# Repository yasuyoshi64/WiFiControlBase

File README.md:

# sdkconfig
Serial flasher config

	Flash size				4MB

Partition Table

	Patition Table			Single factory app (large), no OTA

WiFiControlBase

	LED GPIO number			5

SD card PIN configuration

	MOSI GPIO number		17
	MOSO GPIO number		19
	CLK GPIO number			18
	CS GPIO number			16
	SD card sw GPIO number	4

OLED(SSD1306) PIN configuration

	I2C SDA GPIO number		21
	I2C SCL GPIO number		22

HTTP Server

	WebSocket server support	TRUE

FAT Filesystem support

	Long filename support	Long filename buffer in heap
	OEM Code Page			Japanese (DBCS) (CP932)

Color settings

	Color depth.			1: 1 byte per pixel

Font usage

Enable built-in fonts

	Enable UNSCII 8 (Perfect monospace font)	TRUE

3rd Party Libraries

	QR code library			TRUE

# 機能

## SDカードの内容

### ./config

```
ssid=[Wi-Fi SSID]
pass=[Wi-Fi Password]
```

### ./document

ここにはWeb用のファイルを格納します。

## 使い方

* 「No file」と表示されている場合はSDカードを挿入します。
* 「Wi-Fi Connecting」はWi-Fi接続中です。
* Wi-Fi接続完了後はQRコードが表示されます。QRコードを読み込むとWebのURLが読み込まれ、documentのWebが表示されます。
* QRコードは30秒で消灯します。GPIO0のボタンを押下すると再度30秒表示されます。
* SDカードは電源ON中でも抜き差し可能です。

## 回路図

## Web画面

ロード時にIPアドレスやチップ情報などを読み込み。
メモを入力してSaveボタンをクリックするとSDカードのsaveファイルに格納されます。
メモは再ロード時に読み込まれます。

# _Sample project_

(See the README.md file in the upper level 'examples' directory for more information about examples.)

This is the simplest buildable example. The example is used by command `idf.py create-project`
that copies the project to user specified path and set it's name. For more information follow the [docs page](https://docs.espressif.com/projects/esp-idf/en/latest/api-guides/build-system.html#start-a-new-project)

## How to use example
We encourage the users to use the example as a template for the new projects.
A recommended way is to follow the instructions on a [docs page](https://docs.espressif.com/projects/esp-idf/en/latest/api-guides/build-system.html#start-a-new-project).

## Example folder contents

The project **sample_project** contains one source file in C language [main.c](main/main.c). The file is located in folder [main](main).

ESP-IDF projects are built using CMake. The project build configuration is contained in `CMakeLists.txt`
files that provide set of directives and instructions describing the project's source files and targets
(executable, library, or both). 

Below is short explanation of remaining files in the project folder.

```
├── CMakeLists.txt
├── main
│   ├── CMakeLists.txt
│   └── main.c
└── README.md                  This is the file you are currently reading
```
Additionally, the sample project contains Makefile and component.mk files, used for the legacy Make based build system. 
They are not used or needed when building with CMake and idf.py.

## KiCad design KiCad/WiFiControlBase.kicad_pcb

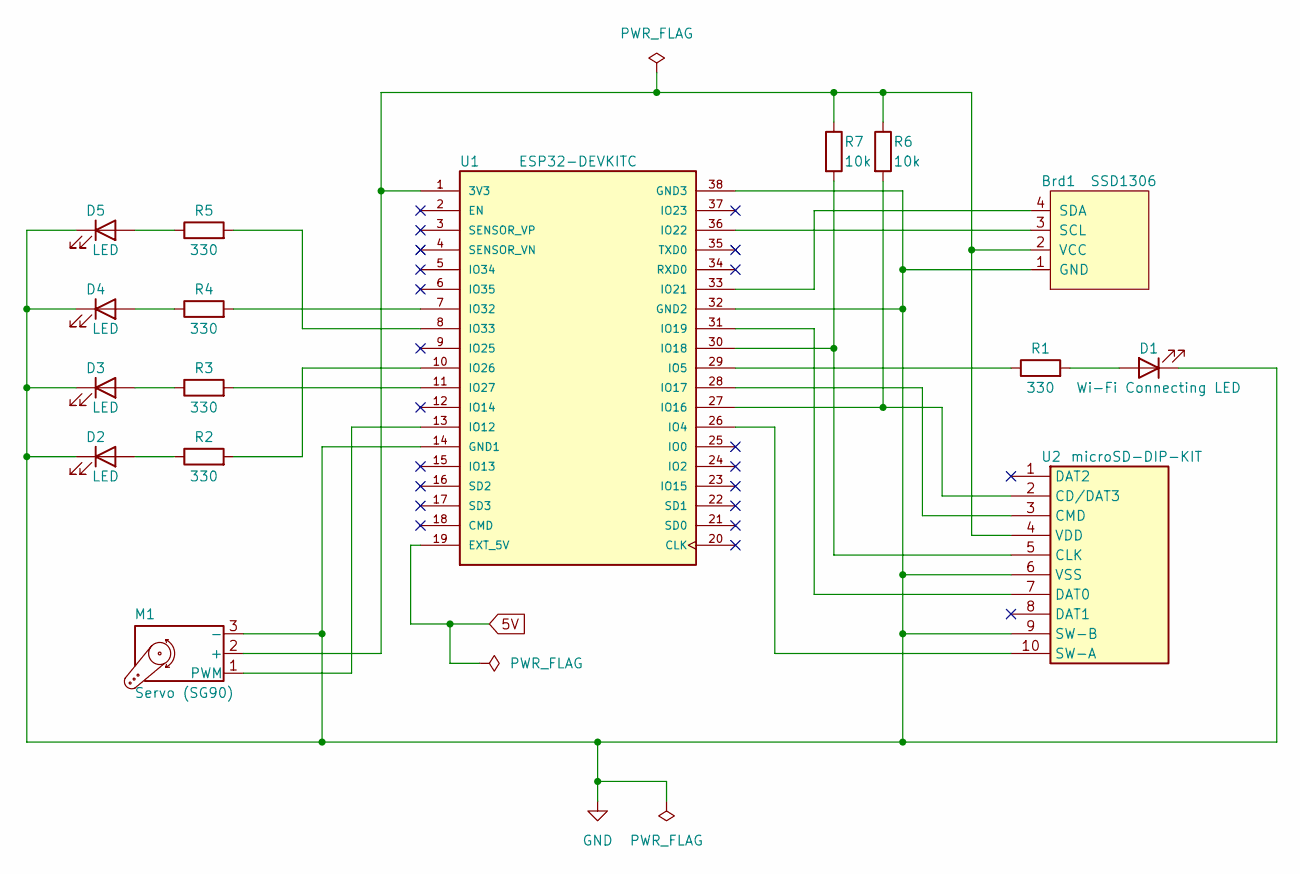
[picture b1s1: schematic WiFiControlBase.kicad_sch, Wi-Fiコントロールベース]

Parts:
Brd1: SSD1306; 128x64OLED
D1: Wi-Fi Connecting LED; LED_D5.0mm
D2, D3, D4, D5: LED; LED_D5.0mm
M1: Servo (SG90); PinHeader_1x03_P2.54mm_Horizontal
R1, R2, R3, R4, R5: 330; R_Axial_DIN0204_L3.6mm_D1.6mm_P5.08mm_Horizontal
R6, R7: 10k; R_Axial_DIN0204_L3.6mm_D1.6mm_P5.08mm_Horizontal
U1: ESP32-DEVKITC; MODULE_ESP32-DEVKITC; PARTREV N/A
U2: microSD-DIP-KIT; microSD-DIP-Kit

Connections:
+3.3V: Brd1.2 (VCC), M1.2 (+), R6.1, R7.1, U1.1 (3V3), U2.4 (VDD)
GND: Brd1.1 (GND), D1.1 (K), D2.1 (K), D3.1 (K), D4.1 (K), D5.1 (K), M1.3 (-), U1.14 (GND1), U1.32 (GND2), U1.38 (GND3), U2.6 (VSS), U2.9 (SW-B)
unnamed: Brd1.3 (SCL), U1.36 (IO22)
unnamed: Brd1.4 (SDA), U1.33 (IO21)
unnamed: D1.2 (A), R1.2
unnamed: D2.2 (A), R2.1
unnamed: D3.2 (A), R3.1
unnamed: D4.2 (A), R4.1
unnamed: D5.2 (A), R5.1
unnamed: M1.1 (PWM), U1.13 (IO12)
unnamed: U1.26 (IO4), U2.10 (SW-A)
unnamed: R1.1, U1.29 (IO5)
unnamed: R6.2, U1.27 (IO16), U2.2 (CD/DAT3)
unnamed: U1.28 (IO17), U2.3 (CMD)
unnamed: R7.2, U1.30 (IO18), U2.5 (CLK)
unnamed: U1.31 (IO19), U2.7 (DAT0)
unnamed: R2.2, U1.10 (IO26)
unnamed: R3.2, U1.11 (IO27)
unnamed: R4.2, U1.7 (IO32)
unnamed: R5.2, U1.8 (IO33)

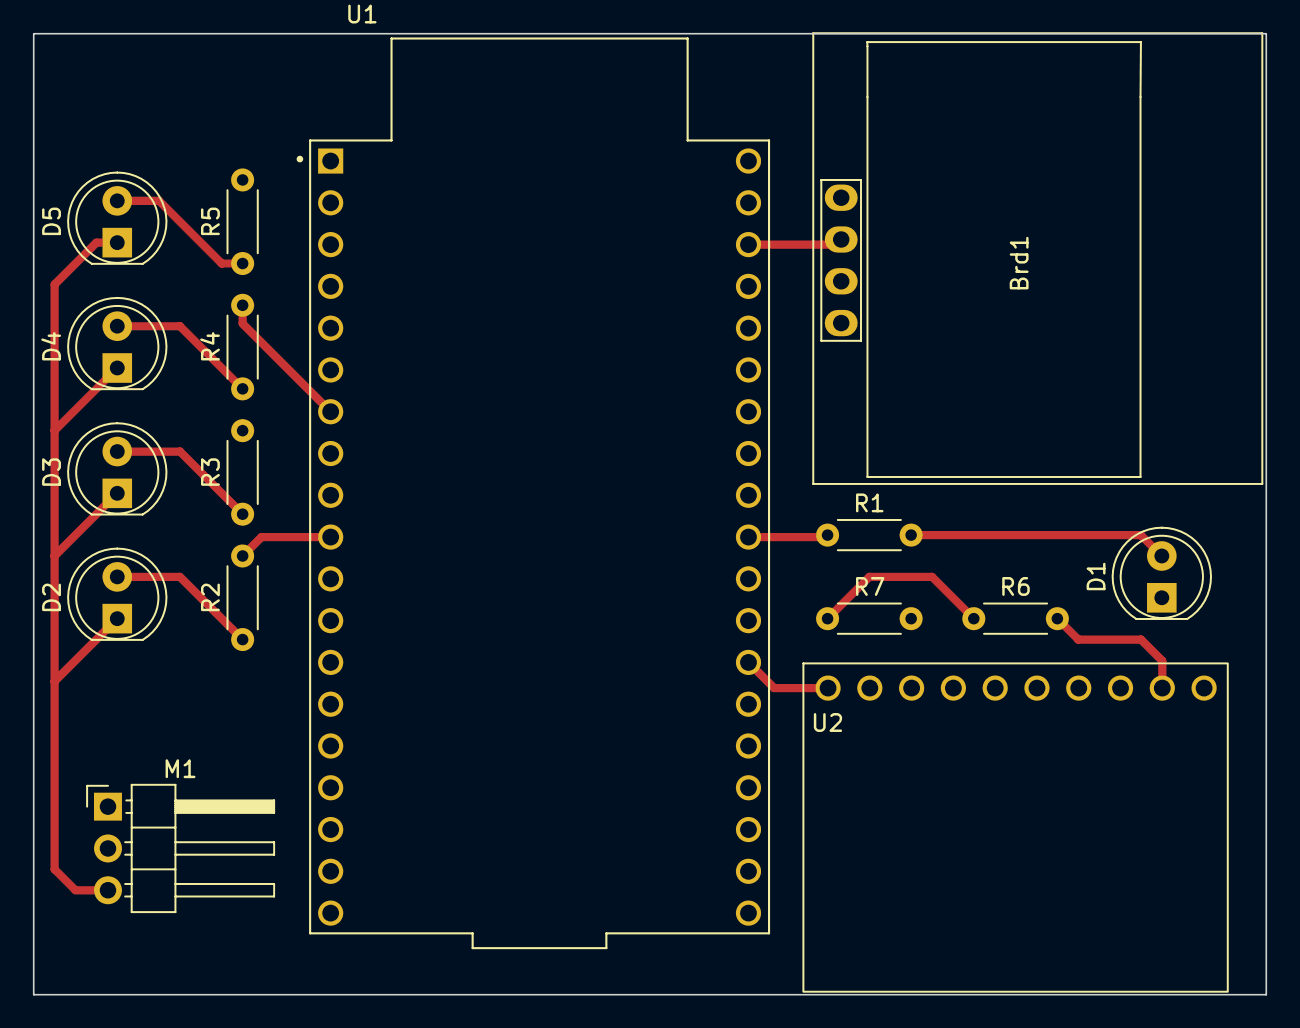
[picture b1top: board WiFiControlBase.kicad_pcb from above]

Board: 2 copper layers, 74.9 x 58.4 mm, 16 parts (0 on the bottom side), 20 nets.

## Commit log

2024-02-26 初期コミット
2024-02-26 web読み込み時にsdカードのdocumentフォルダ直下のhtmlファイル読みに行くように修正。
2024-03-02 4つのLEDを操作できるようにWebAPIを追加
2024-03-10 サーボを操作できるWebAPI & WebSocketを追加
    ・サーボを操作できるWebAPI & WebSocketを追加
    ・KiCadの回路図を追加
2024-03-10 少し説明追加
2024-03-11 トリム値の保存機能を追加
2024-03-11 電源ON時にサーボトリム値読み込み
2024-03-11 フロント(Vue3)を追加
2024-03-11 KiCadのファイル名変更
2024-03-22 余計なものを削除
2024-03-22 説明を追加
